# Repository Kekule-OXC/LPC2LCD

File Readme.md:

# LPC2LCD

This is a custom board that implements the [AladdinLPC](https://github.com/Ryzee119/AladdinLCD) code written by Ryzee119. Gerbers are available [here](eagle/LPC2LCD_v1_gerbers.zip), and all Eagle design files can be found in the eagle directory

This VHDL was writtenby Ryzee119 to replace the CPLD logic on the cheap AladdinXT 4032 Original Xbox modchip.  The pins have been remapped though to allow a cleaner layout on the PCB.  This is best used with a TSOP flashed console. Soft modded functionality unverified.

The Lattice LC4032V CPLD  is extremely limited, so this is a bare minimum to reduce macro-cell usage to fit onto the CPLD. Therefore it will not support any other functionality.

-   This is **NOT** a modchip.
-   This does not support adjusting the backlight via the dashboard settings.
-   This has no contrast control through the dashboard settings. Use the on board trim pot to set the desired contrast.

# Instructions

1.  Connect a JTAG programmer to the JTAG pins.
    
2.  Make sure to apply 3.3V power to the LPC2PCB board. This can be done by plugging it into the LPC port on the Xbox, an external power supply, or a JTAG programmer that can supply power.  A modified Lattice USB programmer clone or FlashCat are two examples of programmers that can supply power.
    
3.  Program the CPLD with the  `SVF`  file in this repository . It can be programmed with  [UrJTAG](http://urjtag.org/)  using a  [compatible programming cable](http://urjtag.org/book/_system_requirements.html#_supported_jtag_adapters_cables). The general programming sequence in UrJTAG is something like: (Commands written in  **bold**).
    
    **cable usbblaster**  _Type  `help cable`  for other supported cables._  
    **detect**  _To confirm that the cpld is detected._  
    **svf LPC2LCD.SVF progress**  _To program the CPLD._
        
4.  Remove the JTAG programming points.
    
5.  Remove the flash memory and socket from the Aladdin Chip to expose the required usable IO pads. Be careful not too damage the pads.
    
6.  Wire the LCD.
    
7.  Install onto the LPC header in your Xbox. There is no other connections to worry about.  _If you have a 1.6 motherboard you will need to rebuild the LPC as you would for a modchip install.  **Don't**  ground any D0 points etc._
    
8.  Enable  `SmartXX`  LCD in your dashboard.
    
9.  Use the trim pot on the top of the board to set the desired contrast

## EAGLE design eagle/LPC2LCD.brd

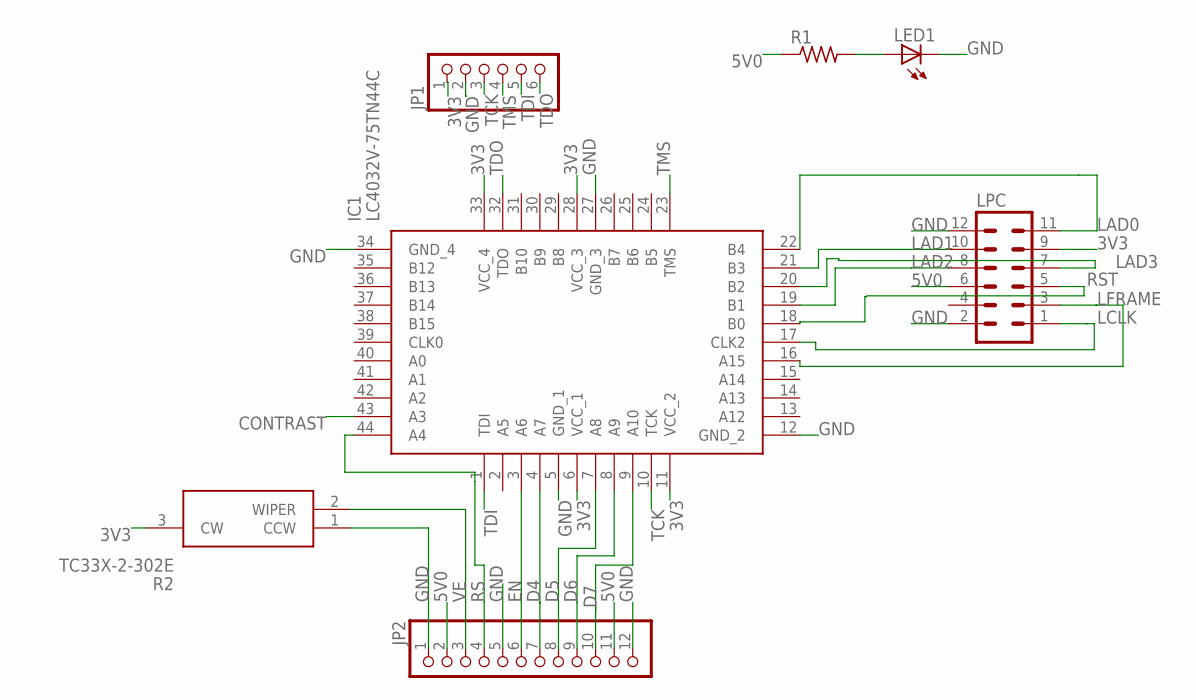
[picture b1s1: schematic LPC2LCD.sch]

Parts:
IC1: LC4032V-75TN44C; QFP80P1200X1200X120-44N
JP1: PINHD-1X6B; 1X06-BIG
JP2: PINHD-1X12; 1X12
LED1: LEDCHIPLED_0805; CHIPLED_0805
LPC: MA06-2
R1: R-US_R0805; R0805
R2: TC33X-2-302E; TC33X-2

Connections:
3V3: IC1.6 (VCC_1), IC1.11 (VCC_2), IC1.28 (VCC_3), IC1.33 (VCC_4), JP1.1, LPC.9, R2.3 (CW)
5V0: JP2.2, JP2.11, LPC.6, R1.1
CONTRAST: IC1.43 (A3)
D4: IC1.4 (A7), JP2.7
D5: IC1.7 (A8), JP2.8
D6: IC1.8 (A9), JP2.9
D7: IC1.9 (A10), JP2.10
EN: IC1.3 (A6), JP2.6
GND: IC1.5 (GND_1), IC1.12 (GND_2), IC1.27 (GND_3), IC1.34 (GND_4), JP1.2, JP2.1, JP2.5, JP2.12, LED1.C, LPC.2, LPC.12, R2.1 (CCW)
LAD0: IC1.22 (B4), LPC.11
LAD1: IC1.21 (B3), LPC.10
LAD2: IC1.19 (B1), LPC.8
LAD3: IC1.20 (B2), LPC.7
LCLK: IC1.17 (CLK2), LPC.1
LFRAME: IC1.16 (A15), LPC.3
unnamed: LED1.A, R1.2
RS: IC1.44 (A4), JP2.4
RST: IC1.18 (B0), LPC.5
TCK: IC1.10 (TCK), JP1.3
TDI: IC1.1 (TDI), JP1.5
TDO: IC1.32 (TDO), JP1.6
TMS: IC1.23 (TMS), JP1.4
VE: JP2.3, R2.2 (WIPER)

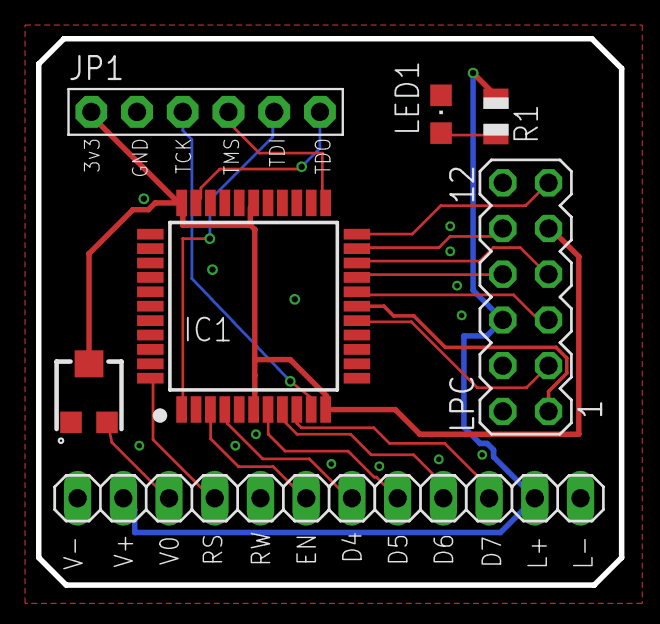
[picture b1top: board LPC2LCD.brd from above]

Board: 2 copper layers, 32.4 x 30.4 mm, 8 parts (1 on the bottom side), 22 nets.

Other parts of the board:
U$1: KEKULE-0002

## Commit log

2020-01-21 initial upload
2020-01-21 Create temp
2020-01-21 added readme
2020-01-21 Create t
